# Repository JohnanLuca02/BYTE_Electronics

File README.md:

# BYTE_Electronics
Repository for everything concerning the electronics (PCB, Electrical schemes, BOM, ...) of the robot dog project of the AiTeam called BYTE.

**READ BEFORE STARTING TO WORK**

**Github workflow:**

*ALWAYS* work on your own branch
1) Check that you're in the correct branch:
   - git branch --all
       - if your branch is highlated in *green*, you can go to step 2)
       - if your branch is highlated in *red*, follow the next steps:
           - git fetch --all
           - git checkout [*name of your branch*]
     
2) Once you're in the right branch, *always* start pulling the changes:
   - git pull 
3) Often save your progress:
   - git add .
   - git commit -m "[*Message describing the changes made*]"
4) At the end of your session, ore once you're happy with your work, push your progress on the repo:
   - git push
  
**FOR EASYEDA2KICAD PLUG-IN**

easyeda2kicad --full --lcsc_id [LCSC CODE] --output .

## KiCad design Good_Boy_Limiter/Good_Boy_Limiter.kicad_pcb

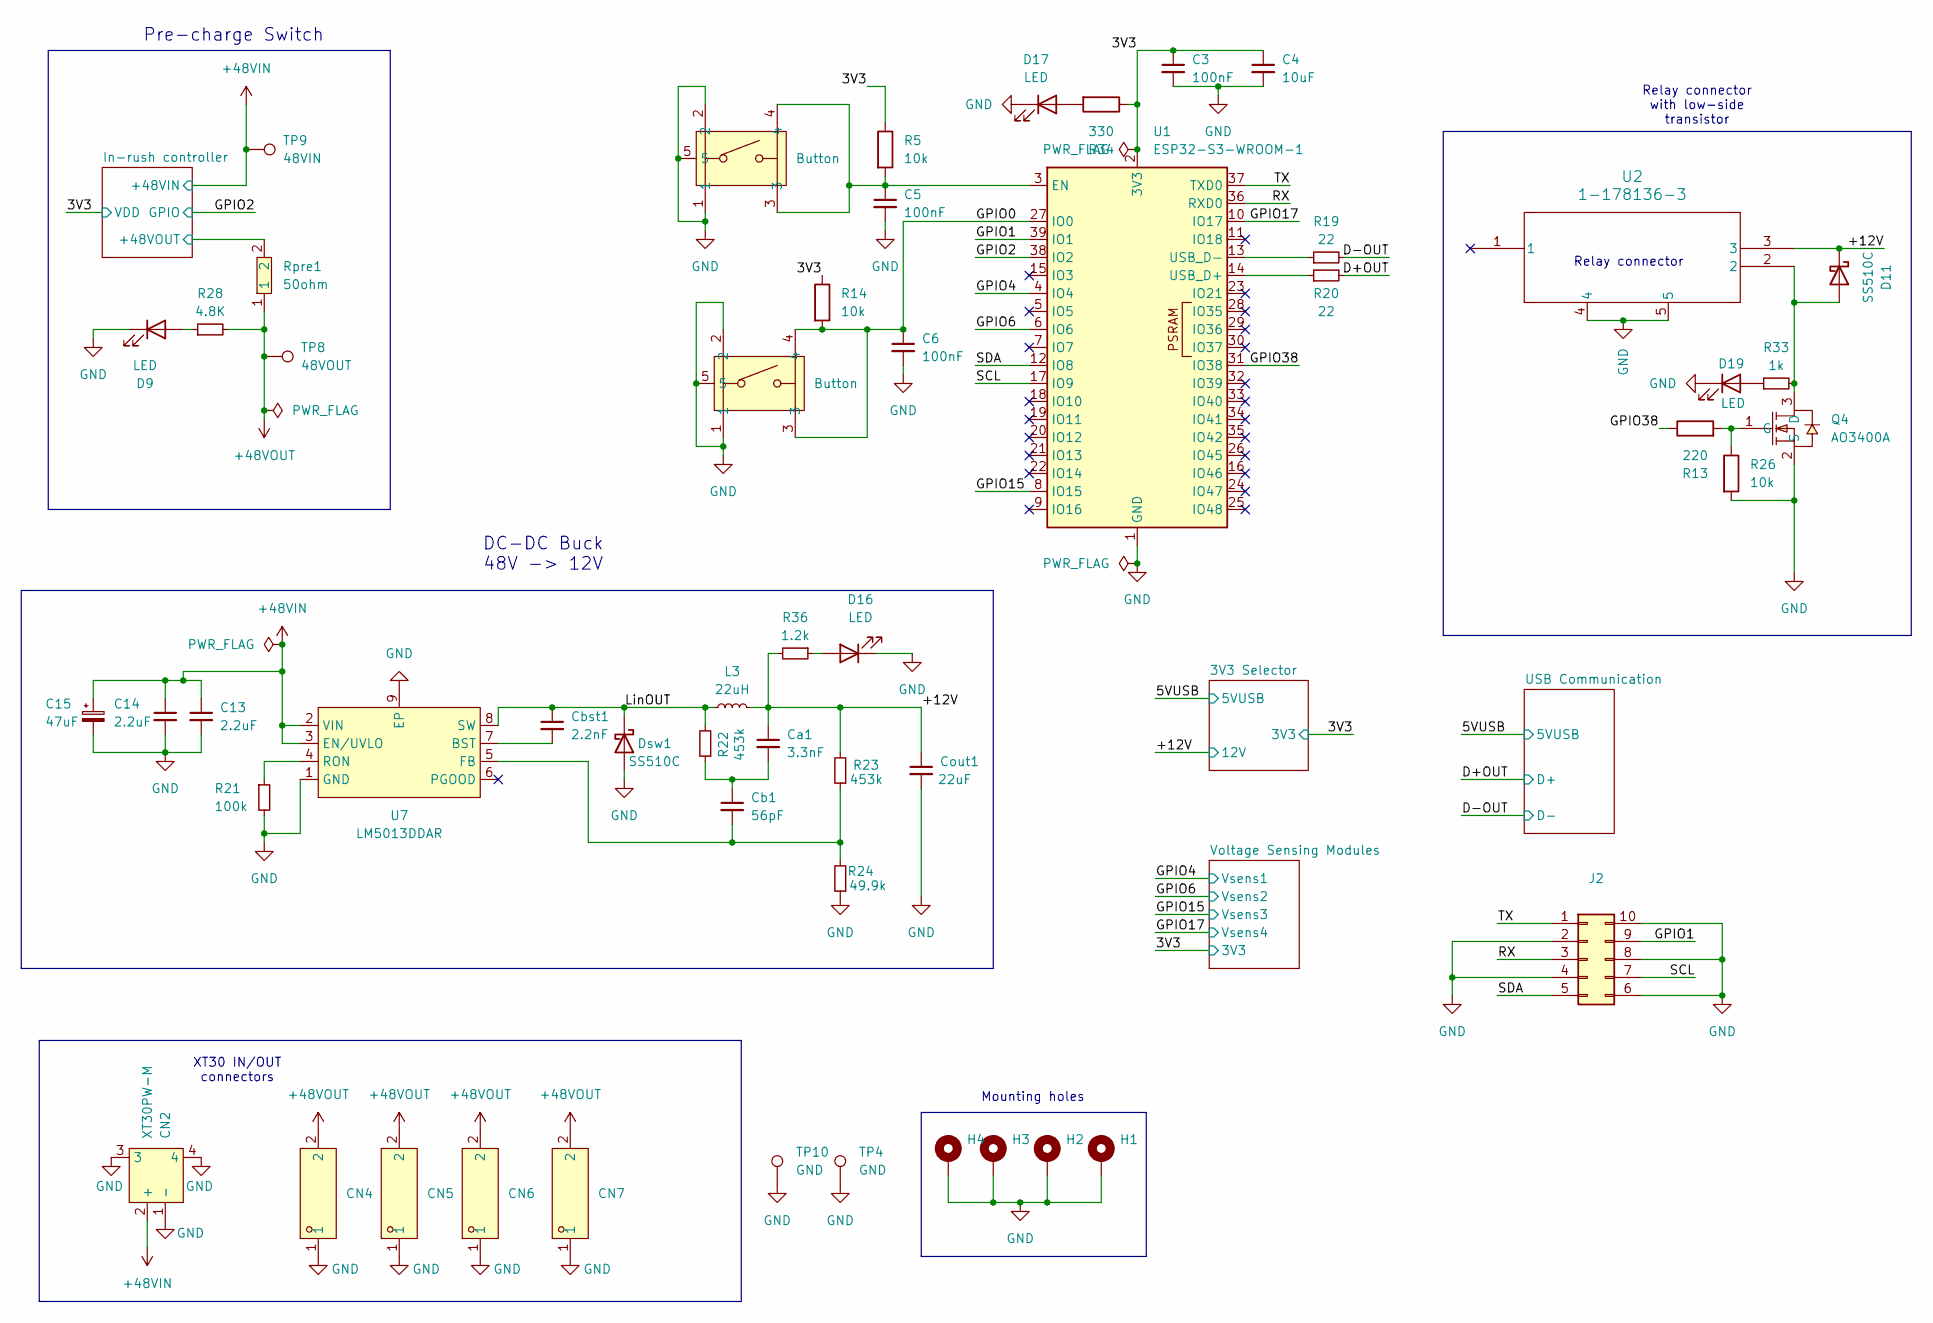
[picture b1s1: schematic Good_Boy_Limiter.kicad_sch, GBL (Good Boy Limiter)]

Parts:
C3: 100nF; C_0603_1608Metric; LCSC Part C1590
C4: 10uF; C_0603_1608Metric; LCSC Part C1691
C5, C6: 100nF; C_0402_1005Metric; LCSC Part C1525
C13, C14: 2.2uF; C_1206_3216Metric; LCSC Part C577211
C15: 47uF; CAP-SMD_BD10.0-L10.3-W10.3-LS11.0-R-RD; LCSC Part C164068
CN2: XT30PW-M; CONN-TH_XT30PW-M; MPN XT30PW-M30.G.Y; LCSC Part C431092
CN4, CN5, CN6, CN7: XT30UW-F.G.Y; CONN-TH_XT30UW-F.G.Y; MPN XT30UW-F.G.Y; LCSC Part C19268025
Ca1: 3.3nF; C_0603_1608Metric; LCSC Part C1613
Cb1: 56pF; C_0603_1608Metric; LCSC Part C39148
Cbst1: 2.2nF; C_0603_1608Metric; LCSC Part C1604
Cout1: 22uF; C_1210_3225Metric; LCSC Part C5341638
D9: LED; LED_0805_2012Metric_Pad1.15x1.40mm_HandSolder; LCSC Part C2295
D11: SS510C; D_SMC; LCSC Part C19229
D16: LED; LED_0805_2012Metric_Pad1.15x1.40mm_HandSolder; LCSC Part C110371
D17: LED; LED_0805_2012Metric_Pad1.15x1.40mm_HandSolder; LCSC Part C2296
D19: LED; LED_0805_2012Metric_Pad1.15x1.40mm_HandSolder; LCSC Part C2297
Dsw1: SS510C; D_SMC; LCSC Part C19229
H1, H2, H3, H4: MountingHole_Pad; MountingHole_3.2mm_M3_Pad_Via
J2: Extra General Pins; PinHeader_2x05_P2.54mm_Vertical
L3: 22uH; IND-SMD_L11.5-W10.0; LCSC Part C149546
Q4: AO3400A; SOT-23-3_L2.9-W1.3-P1.90-LS2.4-BR; MPN AO3400A; LCSC Part C20917
R5, R14, R26: 10k; R_0603_1608Metric; LCSC Part C177337
R13: 220; R_0603_1608Metric; LCSC Part C1226
R19, R20: 22; R_0402_1005Metric; LCSC Part C174144
R21: 100k; R_0603_1608Metric_Pad0.98x0.95mm_HandSolder; LCSC Part C25803
R22, R23: 453k; C_0603_1608Metric; LCSC Part C25818
R24: 49.9k; C_0603_1608Metric; LCSC Part C23184
R28: 4.8K; R_0402_1005Metric; LCSC Part C174177
R33: 1k; R_0402_1005Metric; LCSC Part C173697
R34: 330; R_0402_1005Metric; LCSC Part C174156
R36: 1.2k; R_0402_1005Metric; LCSC Part C174261
Rpre1: 50ohm; RES-TH_BD9.0-L36.5-P40.50-D0.8; MPN EWWR0010J50R0T9; LCSC Part C349130
SW3, SW4: Button; KEY-SMD_KMR2XXGXXX; MPN KMR221GLFS; LCSC Part C72443
TP4, TP10: GND; TestPoint_Pad_D2.0mm
TP8: 48VOUT; TestPoint_Pad_D2.0mm
TP9: 48VIN; TestPoint_Pad_D2.0mm
U1: ESP32-S3-WROOM-1; WIRELM-SMD_ESP32-S3-WROOM-1; LCSC Part C2913204
U2: 1-178136-3; 1-178136-3_TYC
U7: LM5013DDAR; ESOP-8_L4.9-W3.9-P1.27-LS6.0-BL-EP-1; MPN LM5013DDAR; LCSC Part C5383001

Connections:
+48VIN: C13.1, C14.1, C15.1, CN2.2 (+), TP9.1, U7.2 (VIN), U7.3 (EN/UVLO); also elsewhere on the board
+48VOUT: CN4.2, CN5.2, CN6.2, CN7.2, R28.2, Rpre1.1, TP8.1
/3V3: C3.1, C4.1, R5.1, R14.1, R34.1, U1.2 (3V3); also elsewhere on the board
/+12V: Ca1.1, Cout1.1, D11.1 (K), L3.2, R23.2, R36.2, U2.3; also elsewhere on the board
/D+OUT: R20.2; also elsewhere on the board
/D-OUT: R19.2; also elsewhere on the board
/GPIO0: C6.1, R14.2, SW4.3, SW4.4, U1.27 (IO0)
/GPIO1: J2.9, U1.39 (IO1)
/GPIO2: U1.38 (IO2); also elsewhere on the board
/GPIO4: U1.4 (IO4); also elsewhere on the board
/GPIO6: U1.6 (IO6); also elsewhere on the board
/GPIO15: U1.8 (IO15); also elsewhere on the board
/GPIO17: U1.10 (IO17); also elsewhere on the board
/GPIO38: R13.1, U1.31 (IO38)
/In-rush controller/+48VOUT: Rpre1.2; also elsewhere on the board
/LinOUT: Cbst1.1, Dsw1.1 (K), L3.1, R22.2, U7.8 (SW)
/RX: J2.3, U1.36 (RXD0)
/SCL: J2.7, U1.17 (IO9)
/SDA: J2.5, U1.12 (IO8)
/TX: J2.1, U1.37 (TXD0)
GND: C3.2, C4.2, C5.2, C6.2, C13.2, C14.2, C15.2, CN2.1 (-), CN2.3, CN2.4, CN4.1, CN5.1, CN6.1, CN7.1, Cout1.2, D9.1 (K), D16.1 (K), D17.1 (K), D19.1 (K), Dsw1.2 (A), H1.1, H2.1, H3.1, H4.1, J2.2, J2.4, J2.6, J2.8, J2.10, Q4.2 (S), R21.2, R24.1, R26.2, SW3.1, SW3.2, SW3.5, SW4.1, SW4.2, SW4.5, TP4.1, TP10.1, U1.1 (GND), U1.40 (GND), U1.41 (GND), U2.4, U2.5, U7.1 (GND), U7.9 (EP); also elsewhere on the board
unnamed: Ca1.2, Cb1.1, R22.1
unnamed: D9.2 (A), R28.1
unnamed: D11.2 (A), Q4.3 (D), R33.2, U2.2
unnamed: D16.2 (A), R36.1
unnamed: D17.2 (A), R34.2
unnamed: D19.2 (A), R33.1
unnamed: Q4.1 (G), R13.2, R26.1
unnamed: C5.1, R5.2, SW3.3, SW3.4, U1.3 (EN)
unnamed: R20.1, U1.14 (USB_D+)
unnamed: R19.1, U1.13 (USB_D-)
unnamed: Cbst1.2, U7.7 (BST)
unnamed: Cb1.2, R23.1, R24.2, U7.5 (FB)
unnamed: R21.1, U7.4 (RON)

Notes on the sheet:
Relay connector with low-side transistor
Pre-charge Switch
Mounting holes
DC-DC Buck 48V -> 12V
XT30 IN/OUT connectors
Relay connector

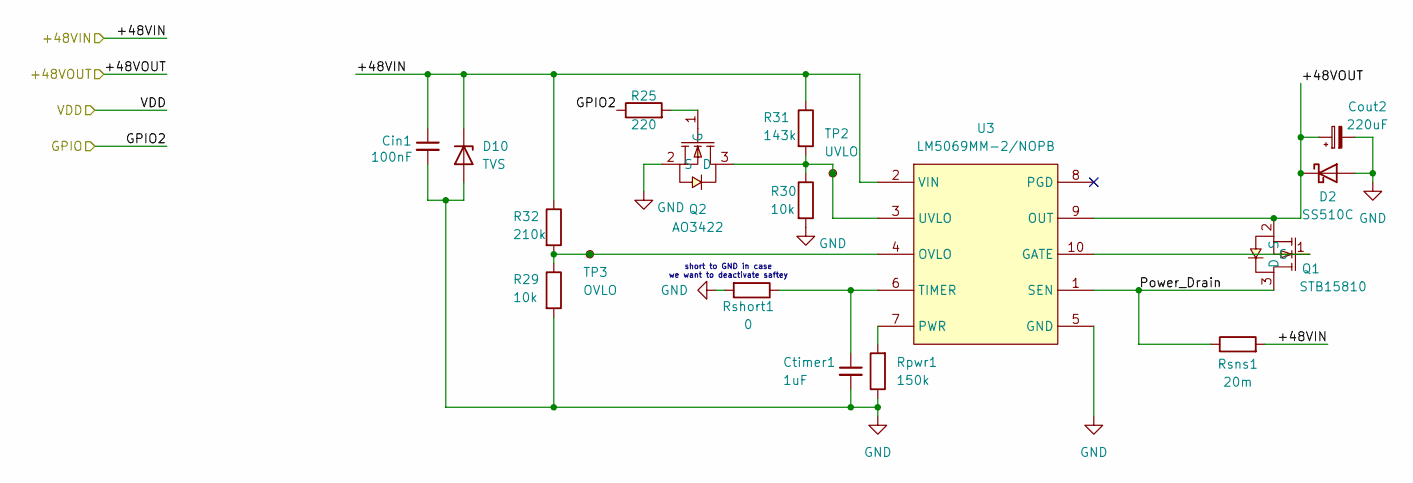
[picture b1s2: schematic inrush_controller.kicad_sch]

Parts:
Cin1: 100nF; C_1206_3216Metric; LCSC Part C1945
Cout2: 220uF; CAP-SMD_BD16.0-L17.0-W17.0-FD; LCSC Part C249883
Ctimer1: 1uF; C_1206_3216Metric; LCSC Part C13832
D2: SS510C; D_SMC; LCSC Part C19229
D10: TVS; D_SMB; LCSC Part C726833
Q1: STB15810; D2PAK_L10.2-W9.0-P5.08-LS16.9-BR; MPN STB15810; LCSC Part C620154
Q2: AO3422; SOT-23_L2.9-W1.3-P1.90-LS2.4-BR; MPN AO3422; LCSC Part C37130
R25: 220; R_0603_1608Metric; LCSC Part C1226
R29, R30: 10k; R_0603_1608Metric_Pad0.98x0.95mm_HandSolder; LCSC Part C25804
R31: 143k; R_0603_1608Metric_Pad0.98x0.95mm_HandSolder; LCSC Part C22877
R32: 210k; R_0603_1608Metric_Pad0.98x0.95mm_HandSolder; LCSC Part C22952
Rpwr1: 150k; R_0603_1608Metric; LCSC Part C22807
Rshort1: 0; R_0603_1608Metric_Pad0.98x0.95mm_HandSolder; LCSC Part C177335
Rsns1: 20m; RES-SMD_L6.4-W3.2-1; LCSC Part C915989
TP2: UVLO; TestPoint_Pad_D1.0mm
TP3: OVLO; TestPoint_Pad_D1.0mm
U3: LM5069MM-2/NOPB; VSSOP-10_L3.0-W3.0-P0.50-LS4.9-BL; MPN LM5069MM-2/NOPB; LCSC Part C111822

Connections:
+48VIN: Cin1.1, D10.1 (K), R31.1, R32.1, Rsns1.2, U3.2 (VIN); also elsewhere on the board
/GPIO2: R25.1; also elsewhere on the board
/In-rush controller/+48VOUT: Cout2.1, D2.1 (K), Q1.2 (S), U3.9 (OUT); also elsewhere on the board
/In-rush controller/Power_Drain: Q1.3 (D), Rsns1.1, U3.1 (SEN)
GND: Cin1.2, Cout2.2, Ctimer1.2, D2.2 (A), D10.2 (A), Q2.2 (S), R29.2, R30.2, Rpwr1.1, Rshort1.2, U3.5 (GND); also elsewhere on the board
unnamed: Q1.1 (G), U3.10 (GATE)
unnamed: Q2.3 (D), R30.1, R31.2, TP2.1, U3.3 (UVLO)
unnamed: Q2.1 (G), R25.2
unnamed: R29.1, R32.2, TP3.1, U3.4 (OVLO)
unnamed: Rpwr1.2, U3.7 (PWR)
unnamed: Ctimer1.1, Rshort1.1, U3.6 (TIMER)

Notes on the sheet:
short to GND in case we want to deactivate saftey

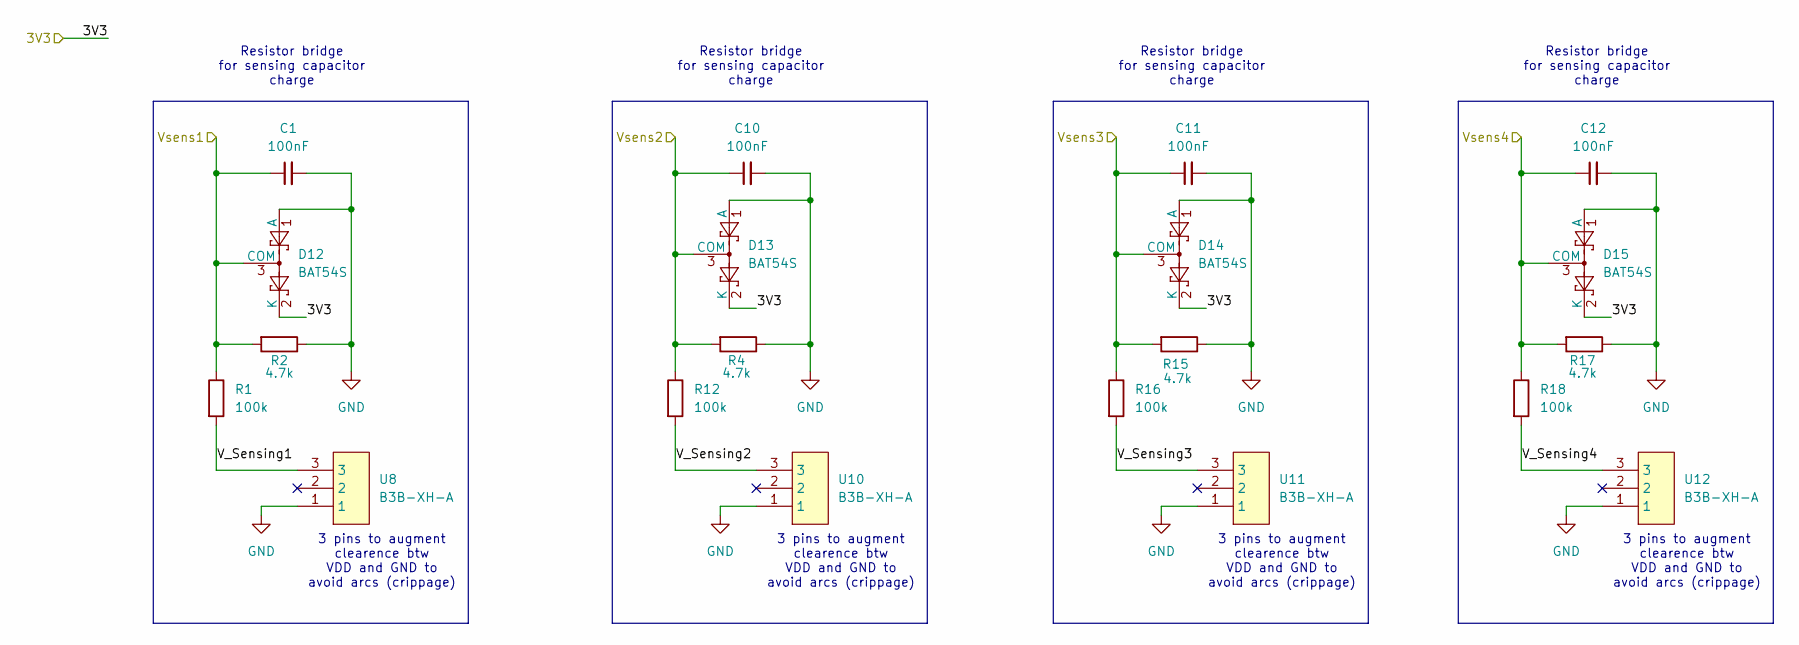
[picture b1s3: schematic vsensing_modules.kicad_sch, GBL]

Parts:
C1, C10, C11, C12: 100nF; C_0603_1608Metric; LCSC Part C1590
D12, D13, D14, D15: BAT54S; SOT-23; LCSC Part C83935
R1, R12, R16, R18: 100k; R_0603_1608Metric_Pad0.98x0.95mm_HandSolder; LCSC Part C25803
R2, R4, R15, R17: 4.7k; R_0603_1608Metric_Pad0.98x0.95mm_HandSolder; LCSC Part C177333
U8, U10, U11, U12: B3B-XH-A; CONN-TH_3P-P2.50_A2501WV2-3P; MPN B3B-XH-A(LF)(SN); LCSC Part C144394

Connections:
/3V3: D12.2 (K), D13.2 (K), D14.2 (K), D15.2 (K); also elsewhere on the board
/GPIO4: C1.1, D12.3 (COM), R1.1, R2.2; also elsewhere on the board
/GPIO6: C10.1, D13.3 (COM), R4.2, R12.1; also elsewhere on the board
/GPIO15: C11.1, D14.3 (COM), R15.2, R16.1; also elsewhere on the board
/GPIO17: C12.1, D15.3 (COM), R17.2, R18.1; also elsewhere on the board
/Voltage Sensing Modules/V_Sensing1: R1.2, U8.3
/Voltage Sensing Modules/V_Sensing2: R12.2, U10.3
/Voltage Sensing Modules/V_Sensing3: R16.2, U11.3
/Voltage Sensing Modules/V_Sensing4: R18.2, U12.3
GND: C1.2, C10.2, C11.2, C12.2, D12.1 (A), D13.1 (A), D14.1 (A), D15.1 (A), R2.1, R4.1, R15.1, R17.1, U8.1, U10.1, U11.1, U12.1; also elsewhere on the board

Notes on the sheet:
3 pins to augment clearence btw VDD and GND to avoid arcs (crippage)
Resistor bridge for sensing capacitor charge

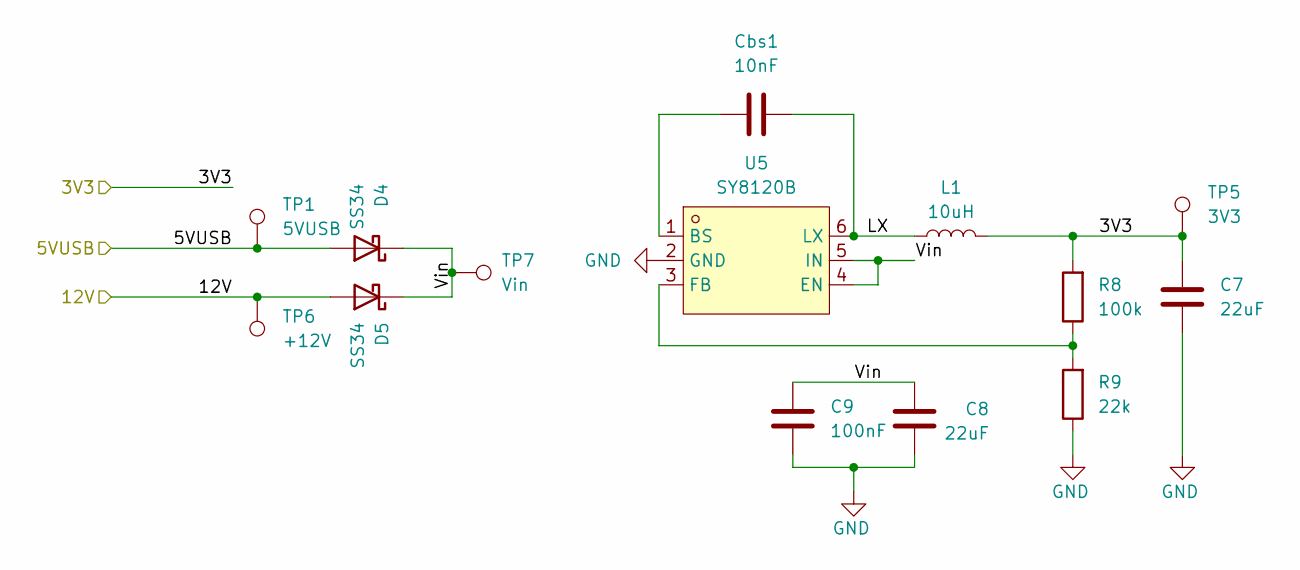
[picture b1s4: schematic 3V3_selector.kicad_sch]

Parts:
C7, C8: 22uF; C_1206_3216Metric_Pad1.33x1.80mm_HandSolder; LCSC Part C12891
C9: 100nF; C_0603_1608Metric; LCSC Part C1590
Cbs1: 10nF; C_0603_1608Metric_Pad1.08x0.95mm_HandSolder; LCSC Part C53084460
D4, D5: SS34; D_SMA_Handsoldering; LCSC Part C8678
L1: 10uH; L_Cenker_CKCS5040; LCSC Part C354610
R8: 100k; R_0603_1608Metric_Pad0.98x0.95mm_HandSolder; LCSC Part C25803
R9: 22k; R_0603_1608Metric_Pad0.98x0.95mm_HandSolder; LCSC Part C177655
TP1: 5VUSB; TestPoint_Pad_D1.0mm
TP5: 3V3; TestPoint_Pad_D1.0mm
TP6: +12V; TestPoint_Pad_D2.0mm
TP7: Vin; TestPoint_Pad_D1.0mm
U5: SY8120B; SOT-23-6_L2.9-W1.6-P0.95-LS2.8-BL; MPN SY8120B; LCSC Part C5330397

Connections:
/3V3: C7.1, L1.2, R8.2, TP5.1; also elsewhere on the board
/3V3 Selector/LX: Cbs1.2, L1.1, U5.6 (LX)
/3V3 Selector/Vin: C8.1, C9.1, D4.1 (K), D5.1 (K), TP7.1, U5.4 (EN), U5.5 (IN)
/5VUSB: D4.2 (A), TP1.1; also elsewhere on the board
/+12V: D5.2 (A), TP6.1; also elsewhere on the board
GND: C7.2, C8.2, C9.2, R9.1, U5.2 (GND); also elsewhere on the board
unnamed: Cbs1.1, U5.1 (BS)
unnamed: R8.1, R9.2, U5.3 (FB)

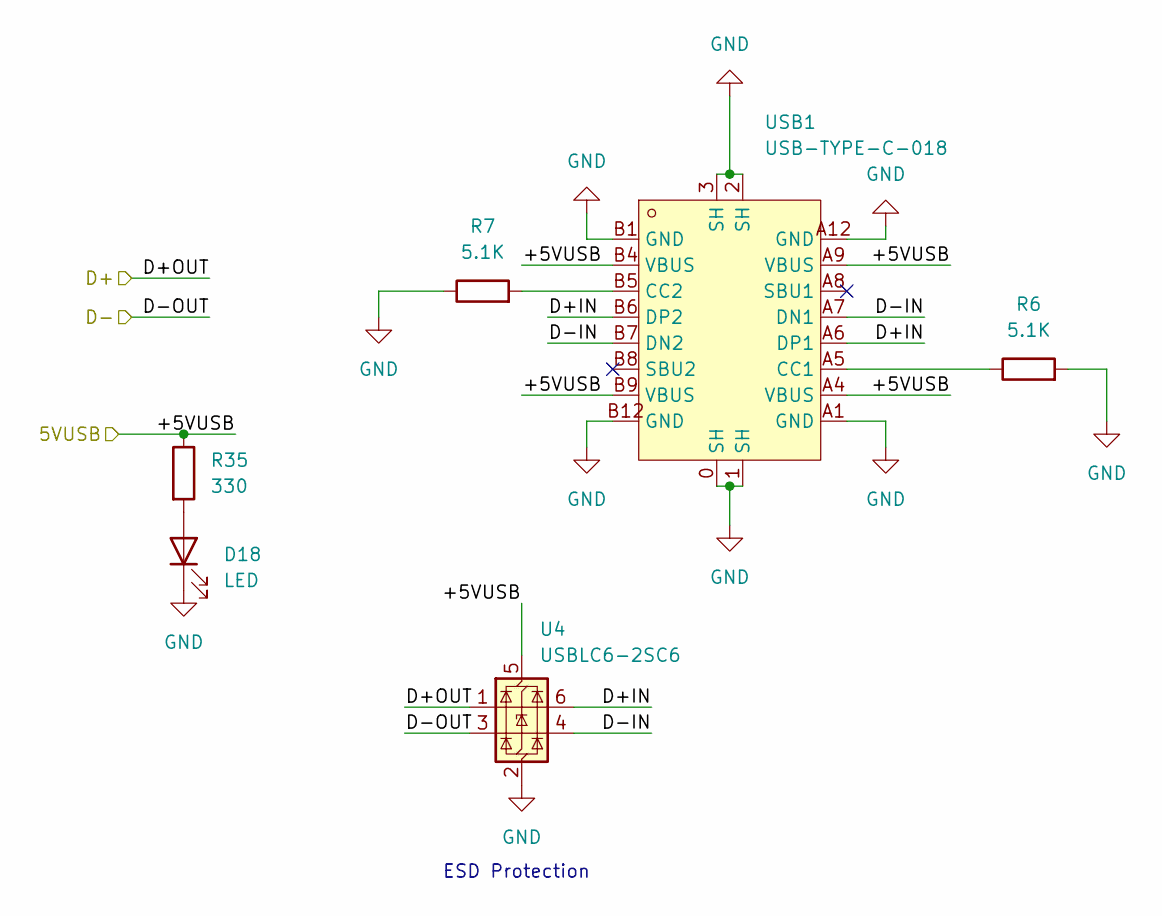
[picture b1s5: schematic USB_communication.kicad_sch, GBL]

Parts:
D18: LED; LED_0805_2012Metric_Pad1.15x1.40mm_HandSolder; LCSC Part C2293
R6, R7: 5.1K; R_0603_1608Metric; LCSC Part C23186
R35: 330; R_0402_1005Metric; LCSC Part C174156
U4: USBLC6-2SC6; SOT-23-6; LCSC Part C7519
USB1: USB-TYPE-C-018; USB-C_SMD-TYPE-C-31-M-12; MPN USB-TYPE-C-018; LCSC Part C2927038

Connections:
/5VUSB: R35.1, U4.5 (VBUS), USB1.A4 (VBUS), USB1.A9 (VBUS), USB1.B4 (VBUS), USB1.B9 (VBUS); also elsewhere on the board
/D+OUT: U4.1 (I/O1); also elsewhere on the board
/D-OUT: U4.3 (I/O2); also elsewhere on the board
/USB Communication/D+IN: U4.6 (I/O1), USB1.A6 (DP1), USB1.B6 (DP2)
/USB Communication/D-IN: U4.4 (I/O2), USB1.A7 (DN1), USB1.B7 (DN2)
GND: D18.1 (K), R6.2, R7.1, U4.2 (GND), USB1.0 (SH), USB1.1 (SH), USB1.2 (SH), USB1.3 (SH), USB1.A1 (GND), USB1.A12 (GND), USB1.B1 (GND), USB1.B12 (GND); also elsewhere on the board
unnamed: D18.2 (A), R35.2
unnamed: R6.1, USB1.A5 (CC1)
unnamed: R7.2, USB1.B5 (CC2)

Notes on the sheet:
ESD Protection

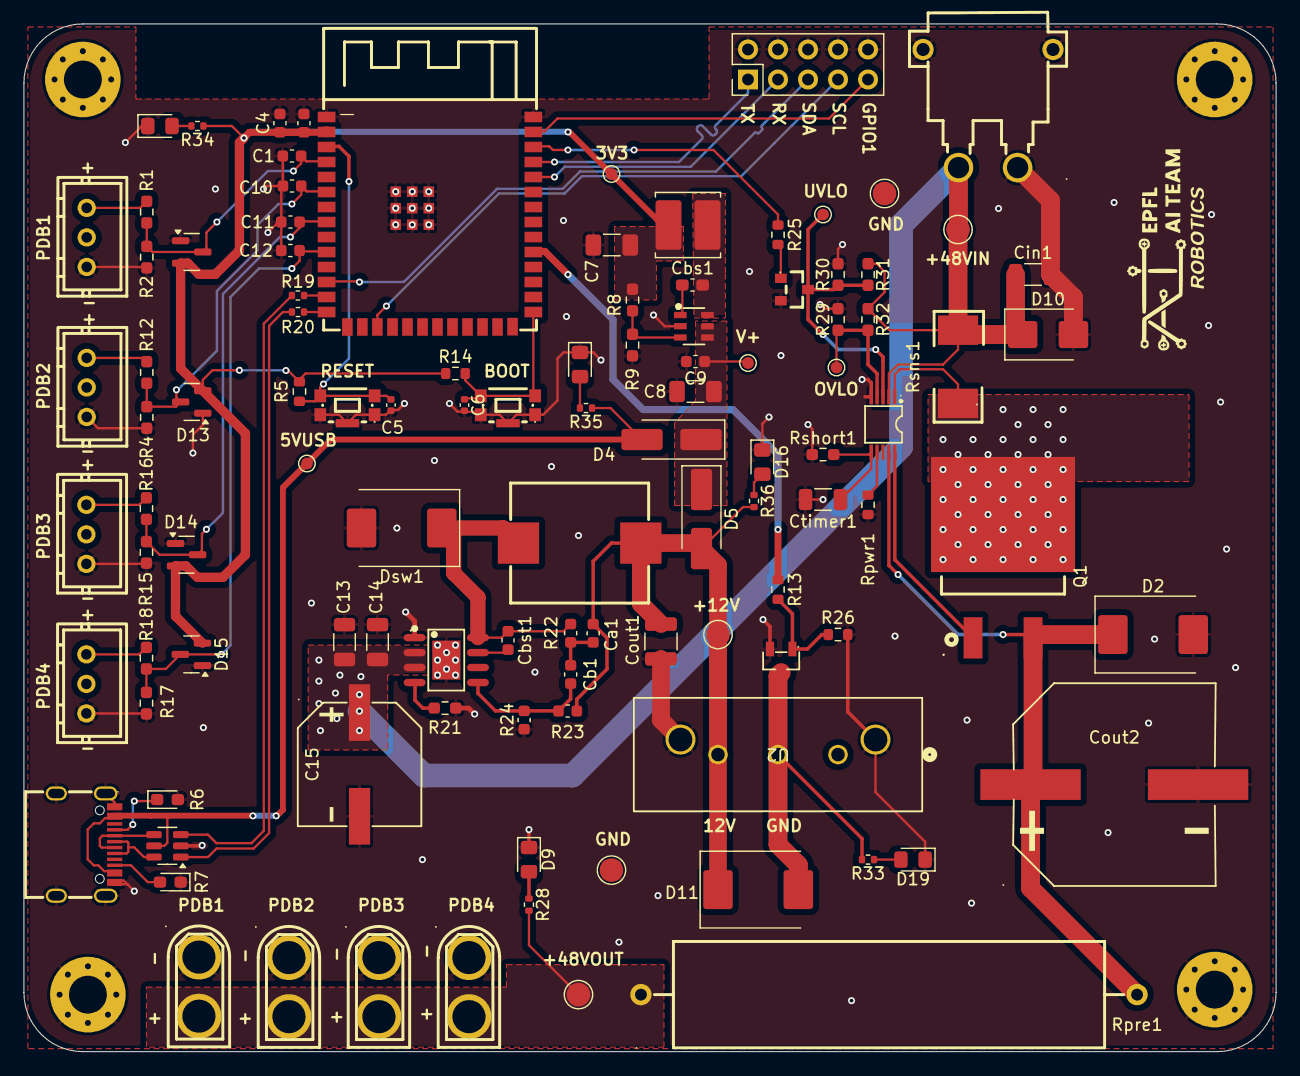
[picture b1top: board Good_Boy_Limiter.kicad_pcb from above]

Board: 2 copper layers, 106.0 x 87.0 mm, 111 parts (0 on the bottom side), 55 nets.

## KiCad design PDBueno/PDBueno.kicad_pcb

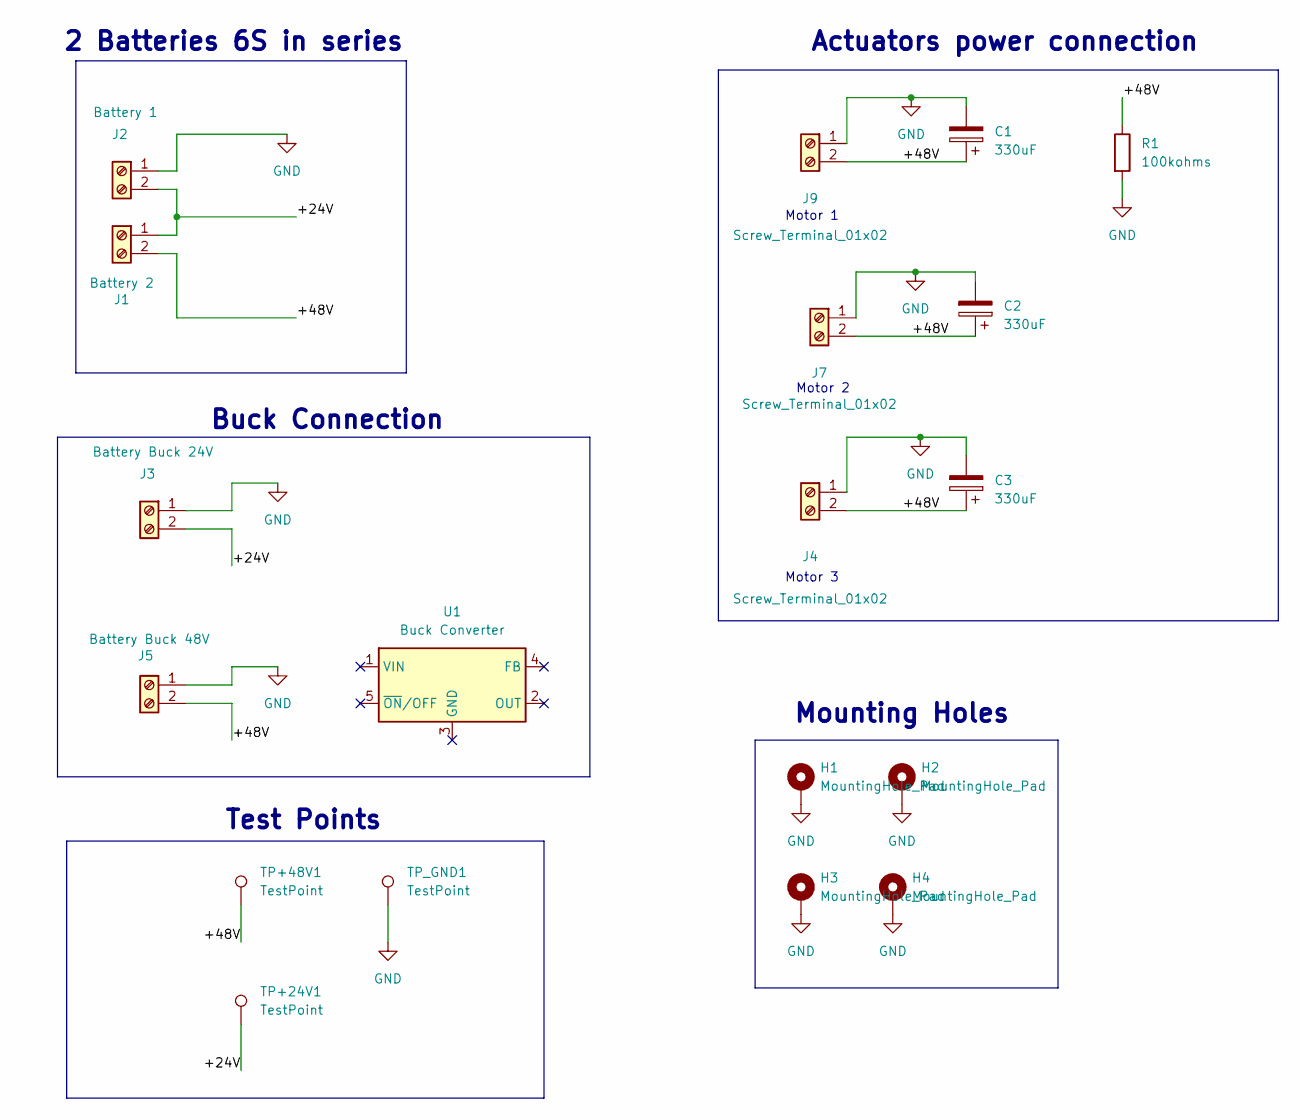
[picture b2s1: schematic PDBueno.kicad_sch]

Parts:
C1, C2, C3: 330uF; VZH331M2ATR-1816
H1, H2, H3, H4: MountingHole_Pad; MountingHole_3.2mm_M3_Pad_Via
J1: Battery 2; AMASS_XT90PW-M_1x02_P10.90mm_Horizontal
J2: Battery 1; AMASS_XT90PW-M_1x02_P10.90mm_Horizontal
J3: Battery Buck 24V; TerminalBlock_bornier-2_P5.08mm
J4, J7, J9: Screw_Terminal_01x02; AMASS_XT30PW-M_1x02_P2.50mm_Horizontal
J5: Battery Buck 48V; TerminalBlock_bornier-2_P5.08mm
R1: 100kohms; R_2512_6332Metric_Pad1.40x3.35mm_HandSolder; LCSC C25717
TP+24V1, TP+48V1: TestPoint; TestPoint_Pad_D4.0mm
TP_GND1: TestPoint; TestPoint_Pad_D4.0mm
U1: Buck Converter; BEC_Matek_12S_Pro

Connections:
/+24V: J1.1, J2.2, J3.2, TP+24V1.1
/+48V: C1.1, C2.1, C3.1, J1.2, J4.2, J5.2, J7.2, J9.2, R1.1, TP+48V1.1
GND: C1.2, C2.2, C3.2, H1.1, H2.1, H3.1, H4.1, J2.1, J3.1, J4.1, J5.1, J7.1, J9.1, R1.2, TP_GND1.1

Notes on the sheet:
Mounting Holes
Actuators power connection
2 Batteries 6S in series
Motor 1
Test Points
Motor 2
Buck Connection
Motor 3

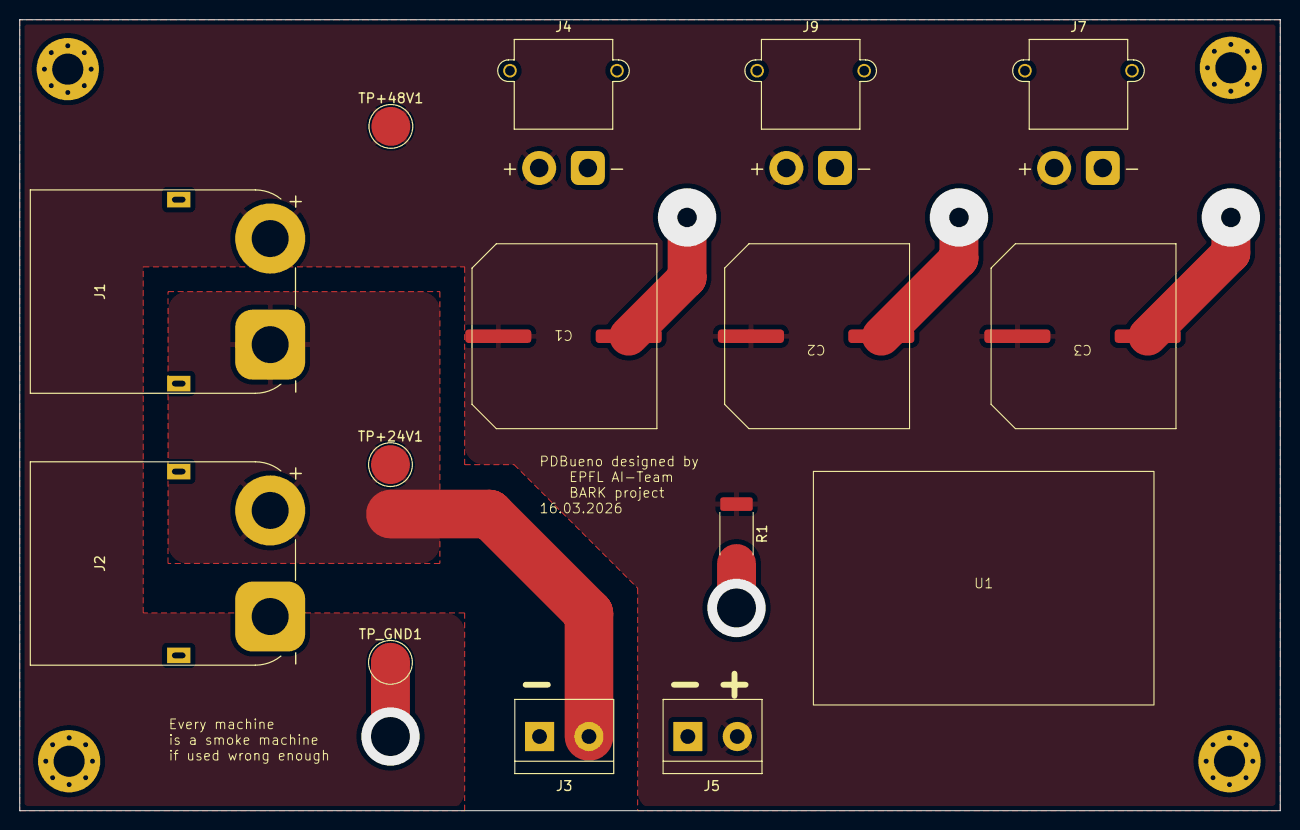
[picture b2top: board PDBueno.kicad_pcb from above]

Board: 2 copper layers, 129.5 x 81.3 mm, 19 parts (0 on the bottom side), 3 nets.

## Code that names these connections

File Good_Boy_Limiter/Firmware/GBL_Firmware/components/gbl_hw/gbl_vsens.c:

/*
 * GBL - PDB voltage sensing
 *
 * Vsens1..4 = GPIO4, GPIO6 (ADC1), GPIO15, GPIO17 (ADC2).
 * Each input has a 100k / 4.7k divider with a 100 nF filter and BAT54S clamps
 * (see "Voltage Sensing Modules" sheet): 48 V -> 2.15 V at the pin, full scale
 * ≈ 69 V with 12 dB attenuation. ADC2 is usable because Wi-Fi is not running.
 */

#include "gbl_vsens.h"

#include "esp_log.h"
#include "esp_adc/adc_oneshot.h"
#include "esp_adc/adc_cali_scheme.h"

#define DIVIDER_RATIO ((100.0f + 4.7f) / 4.7f)
#define OVERSAMPLE 16				 // samples averaged per reading
#define FALLBACK_FULL_SCALE_MV 3100 // linear conversion used only without eFuse calibration

static const char *TAG = "vsens";

static const adc_unit_t ch_unit[GBL_VSENS_CHANNELS] = {ADC_UNIT_1, ADC_UNIT_1, ADC_UNIT_2, ADC_UNIT_2};
static const adc_channel_t ch_adc[GBL_VSENS_CHANNELS] = {ADC_CHANNEL_3, ADC_CHANNEL_5, ADC_CHANNEL_4, ADC_CHANNEL_6};

/* Per-channel gain correction: V_multimeter / V_read, measured with the debug
 * firmware ('V' command). Covers divider tolerance and residual ADC error. */
static const float ch_gain[GBL_VSENS_CHANNELS] = {1.0f, 1.0f, 1.0f, 1.0f};

/* PDBs connected to the pre-charge line. Disabled channels read ~0 V and
 * would otherwise be mistaken for a short. */
static const bool ch_enabled[GBL_VSENS_CHANNELS] = {true, true, true, true}; // PDB1, PDB2, PDB3, PDB4

static adc_oneshot_unit_handle_t unit_handle[2];
static adc_cali_handle_t cali_handle[GBL_VSENS_CHANNELS];

void gbl_vsens_init(void)
{
	for (int u = 0; u < 2; u++)
	{
		adc_oneshot_unit_init_cfg_t cfg = {.unit_id = u == 0 ? ADC_UNIT_1 : ADC_UNIT_2};
		ESP_ERROR_CHECK(adc_oneshot_new_unit(&cfg, &unit_handle[u]));
	}

	adc_oneshot_chan_cfg_t chan_cfg = {.atten = ADC_ATTEN_DB_12, .bitwidth = ADC_BITWIDTH_DEFAULT};
	for (int ch = 0; ch < GBL_VSENS_CHANNELS; ch++)
	{
		ESP_ERROR_CHECK(adc_oneshot_config_channel(unit_handle[ch_unit[ch]], ch_adc[ch], &chan_cfg));

		adc_cali_curve_fitting_config_t cali_cfg = {
			.unit_id = ch_unit[ch],
			.chan = ch_adc[ch],
			.atten = ADC_ATTEN_DB_12,
			.bitwidth = ADC_BITWIDTH_DEFAULT,
		};
		if (adc_cali_create_scheme_curve_fitting(&cali_cfg, &cali_handle[ch]) != ESP_OK)
		{
			cali_handle[ch] = NULL;
			ESP_LOGW(TAG, "PDB%d: no eFuse calibration, using linear conversion", ch + 1);
		}
	}
}

/* Voltage of one channel in volts: averaged raw reading -> eFuse-calibrated
 * millivolts at the pin -> divider ratio -> per-channel gain. Returns -1 on read failure: a negative
 * value always fails the pre-charge checks, so a faulty input can never allow
 * the relay to close. */
static float read_channel(int ch)
{
	int sum = 0;
	for (int k = 0; k < OVERSAMPLE; k++)
	{
		int raw;
		if (adc_oneshot_read(unit_handle[ch_unit[ch]], ch_adc[ch], &raw) != ESP_OK)
			return -1.0f;
		sum += raw;
	}

	int raw = sum / OVERSAMPLE;
	int mv;
	if (!cali_handle[ch] || adc_cali_raw_to_voltage(cali_handle[ch], raw, &mv) != ESP_OK)
		mv = raw * FALLBACK_FULL_SCALE_MV / 4095;
	return mv / 1000.0f * DIVIDER_RATIO * ch_gain[ch];
}

void gbl_vsens_read(gbl_vsens_t *out)
{
	out->valid = false;
	for (int ch = 0; ch < GBL_VSENS_CHANNELS; ch++)
	{
		float v = read_channel(ch);
		out->volt[ch] = v;
		if (!ch_enabled[ch])
			continue;
		if (!out->valid || v < out->min)
			out->min = v;
		if (!out->valid || v > out->max)
			out->max = v;
		out->valid = true;
	}
}

bool gbl_vsens_enabled(int ch)
{
	return ch >= 0 && ch < GBL_VSENS_CHANNELS && ch_enabled[ch];
}

void gbl_vsens_log(const char *tag, const gbl_vsens_t *r)
{
	ESP_LOGI(TAG, "%s: PDB1=%.2fV PDB2=%.2fV PDB3=%.2fV PDB4=%.2fV", tag,
			 r->volt[0], r->volt[1], r->volt[2], r->volt[3]);
}

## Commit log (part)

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2026-03-07 Added empty base files for KiCad
2026-03-10 copie de mon projet kicad
2026-03-10 Footprint added and minor changes
2026-03-13 Update README with GitHub workflow instructions
    Added guidelines for GitHub workflow and branch management.
2026-03-14 Avencement du pcb avec connexions
2026-03-14 PDByte added
2026-03-14 Added PDbyte at right place
2026-03-14 first changes for PDByte
2026-03-14 Added footprint for 330uF capa
2026-03-14 added footprint to compo exept switch and Buck
2026-03-14 corrections
2026-03-14 added folder for PCBueno
2026-03-14 PCB routing
2026-03-16 Renamed PDBueno project files and added SPIne project
2026-03-16 added some basic connection on SPIne
2026-03-16 Added vias to properly connect capacitors to GND
2026-03-16 50th copper pour
2026-03-16 updates updates updates...
2026-03-16 comment
2026-03-17 corrected Electrical scheme with conventions
2026-03-20 did th e project in easyeda to ficilitater orders and added CAN
2026-04-14 Added library from JLCPCB, and GBL folder
2026-04-14 Added schottky and Inductor for DC-DC converter
2026-04-14 Add easyeda2kicad plug-in usage instructions
    Added instructions for using the easyeda2kicad plug-in.
2026-04-15 FIX: Added capacitors for Buck
2026-04-17 Added a lot of stuff, sowwy
2026-04-17 Added some footprints
2026-04-18 Added more footprints
2026-04-18 Added all footprints
2026-04-19 Added mounting holes and test points
2026-04-19 started some routing
2026-04-19 Added PWR-FLag for ERC check
2026-04-20 fix: added 4 voltage sensing modules to measure all the 4 PDBs
2026-04-20 Routing update
2026-04-21 Updated routing
2026-04-21 More update on routing
2026-04-21 Added xt30 adn routed, ready for revision
2026-04-29 Finished e-scheme
2026-04-29 started routing
2026-05-03 routing finished
2026-05-03 DRC fixes
2026-05-05 Added first documentation for GBL
2026-05-05 Added pictures and title page
2026-05-06 Documentation update
2026-05-06 added explications for 3V3 'selector'
2026-05-08 added 3Ds and added more output fore PDBs
2026-05-08 e-scheme update
2026-05-08 Added orange led
2026-05-08 Updated documentation
2026-05-08 Folder cleaning
2026-05-11 Solved DRC and ERC
2026-05-12 fix: removed copper plate in antenna area
2026-05-12 feat: added AIT logo
